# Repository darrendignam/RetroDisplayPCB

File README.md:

# RetroDisplayPCB

This repo is part a wider Tickertape Retro Display project that you can use to create your own Internet of Things LED display with that retro feel.

Check out the website, and my other project for the code library for Arduino and ESP32 for the rest of the project.

* http://tickertape.cc/
* https://github.com/darrendignam/LED_Display_Wrapper

# How the project works

Eagle version 9.1.3 was used on a Windows PC to create these files.
Some of the parts used, were made specifically for this project, and can be found here too.

In addition to the standard libraries the following Eagle libraries were also used:

    holtek-led-controller-v1
    
    Holtek Semiconductor Inc. Devices
    RAM Mapping 16*8 LED Controller Driver with keyscan
    SOP28, SOP24, SOP20
    www.holtek.com
    Created by S.Hofmann mc_sho@gmx.de
    
* http://eagle.autodesk.com/eagle/download/444

Various SparkFun libraries:
    
    SparkFun-Aesthetics
    SparkFun-Capacitors
    SparkFun-Connectors
    SparkFun-LED
    
* https://github.com/sparkfun/SparkFun-Eagle-Libraries
    
All of these are easy to find either in the library manager, or from the github pages for these projects. The sparkfun link has further great information for using Eagle and custom libraries installing them, everything. So I won't try and replicate that here!

# License Information
This library is released under the [Creative Commons ShareAlike 4.0 International license](https://creativecommons.org/licenses/by-sa/4.0/). You are welcome to use this library for commercial purposes. For attribution, we ask that when you begin to sell your device, you email us with a link to the product being sold. It would be great to see where this project goes, and will perhaps feature it on the website.

Together we can help the open-source hardware community continue to thrive and grow!

This project uses the 1206 LED footprint and some other helpful parts from the SparkFun projects listed above to help with the project. None of them were modified, they were used as-is.

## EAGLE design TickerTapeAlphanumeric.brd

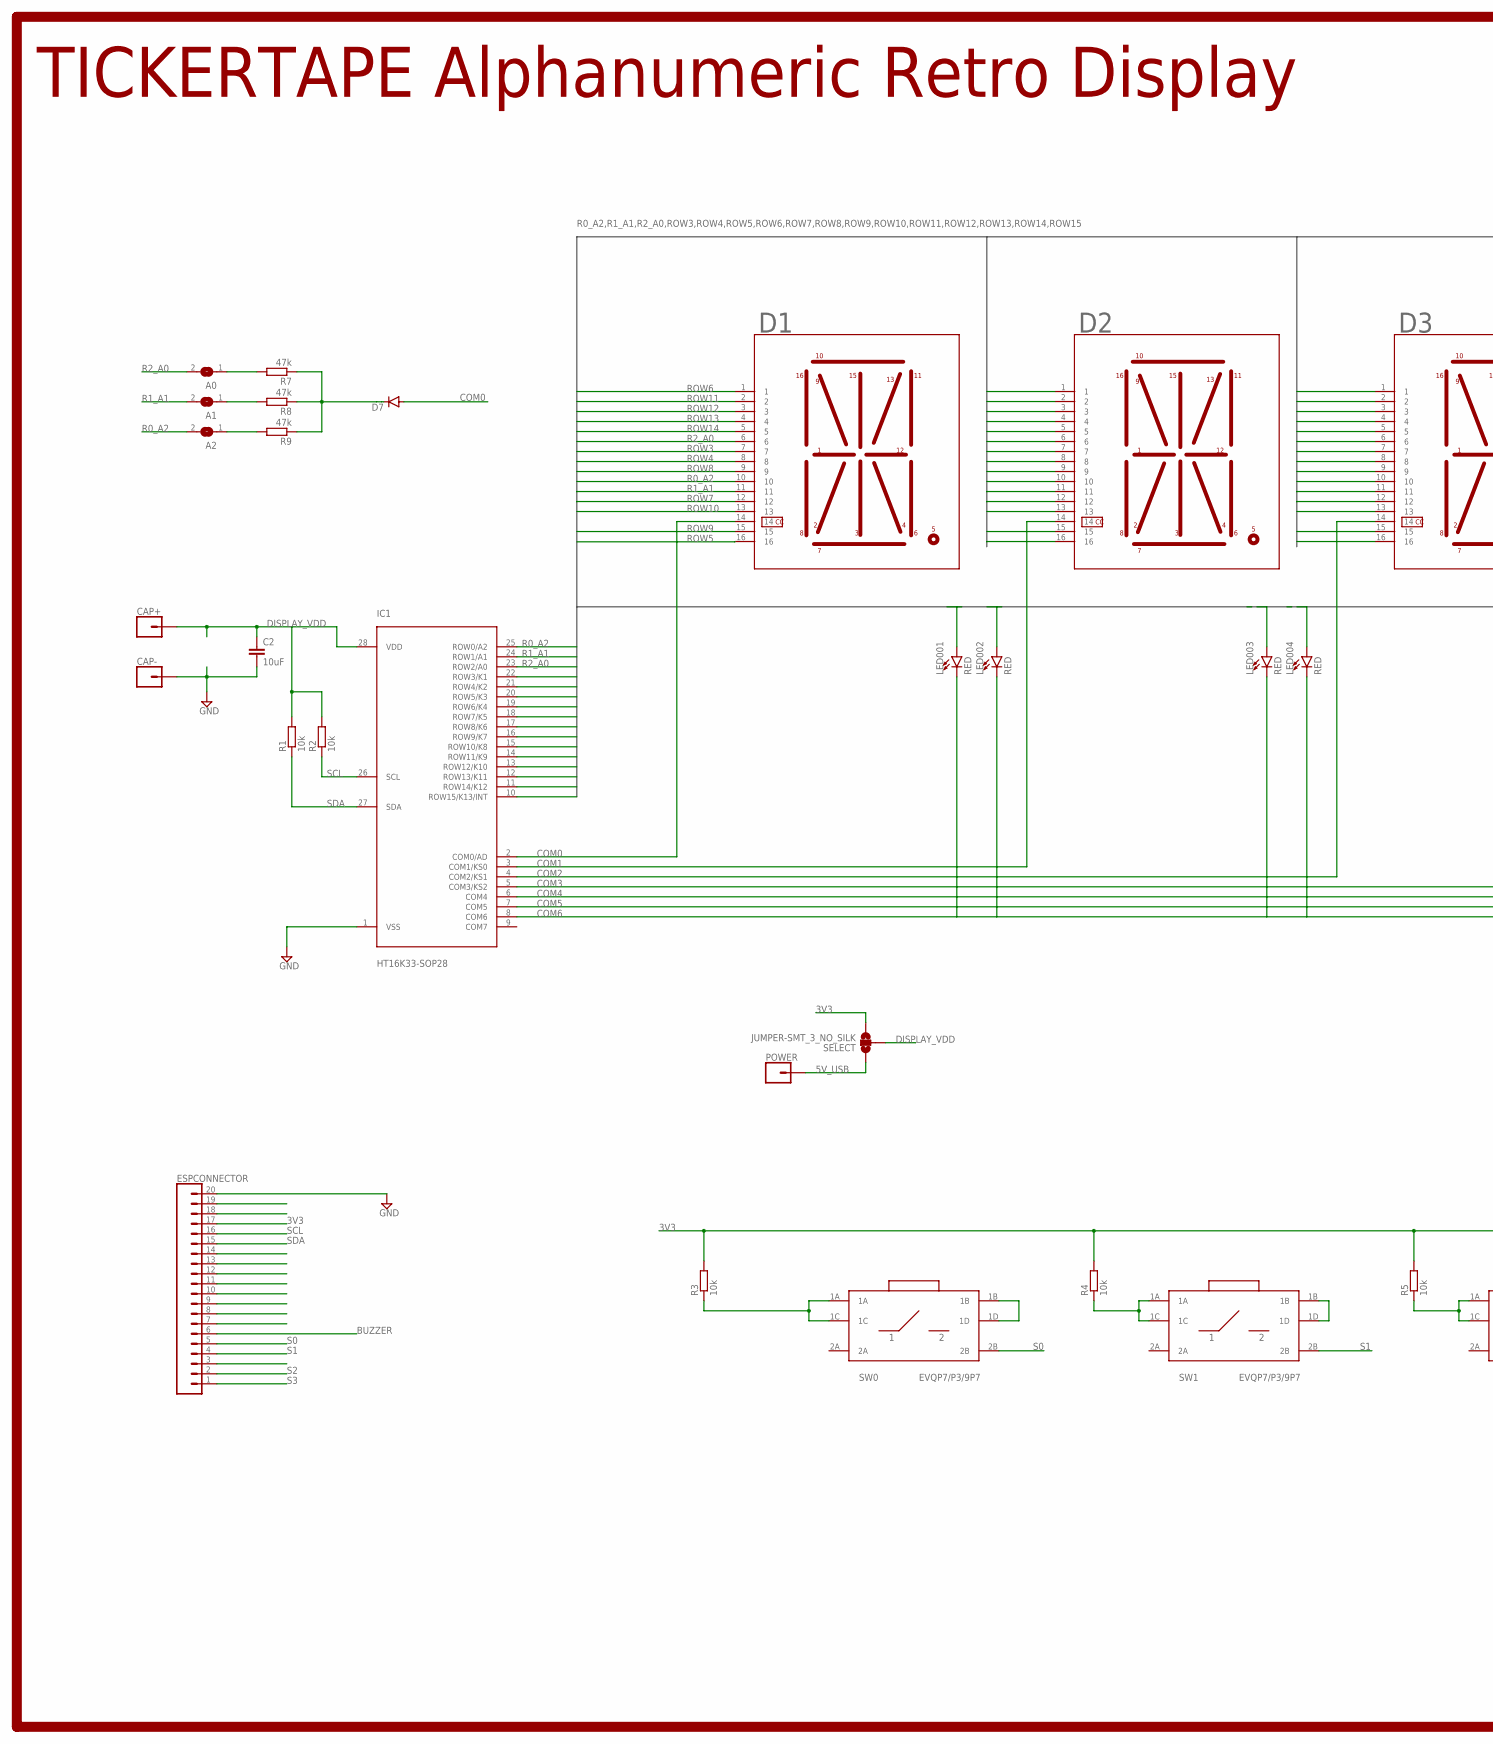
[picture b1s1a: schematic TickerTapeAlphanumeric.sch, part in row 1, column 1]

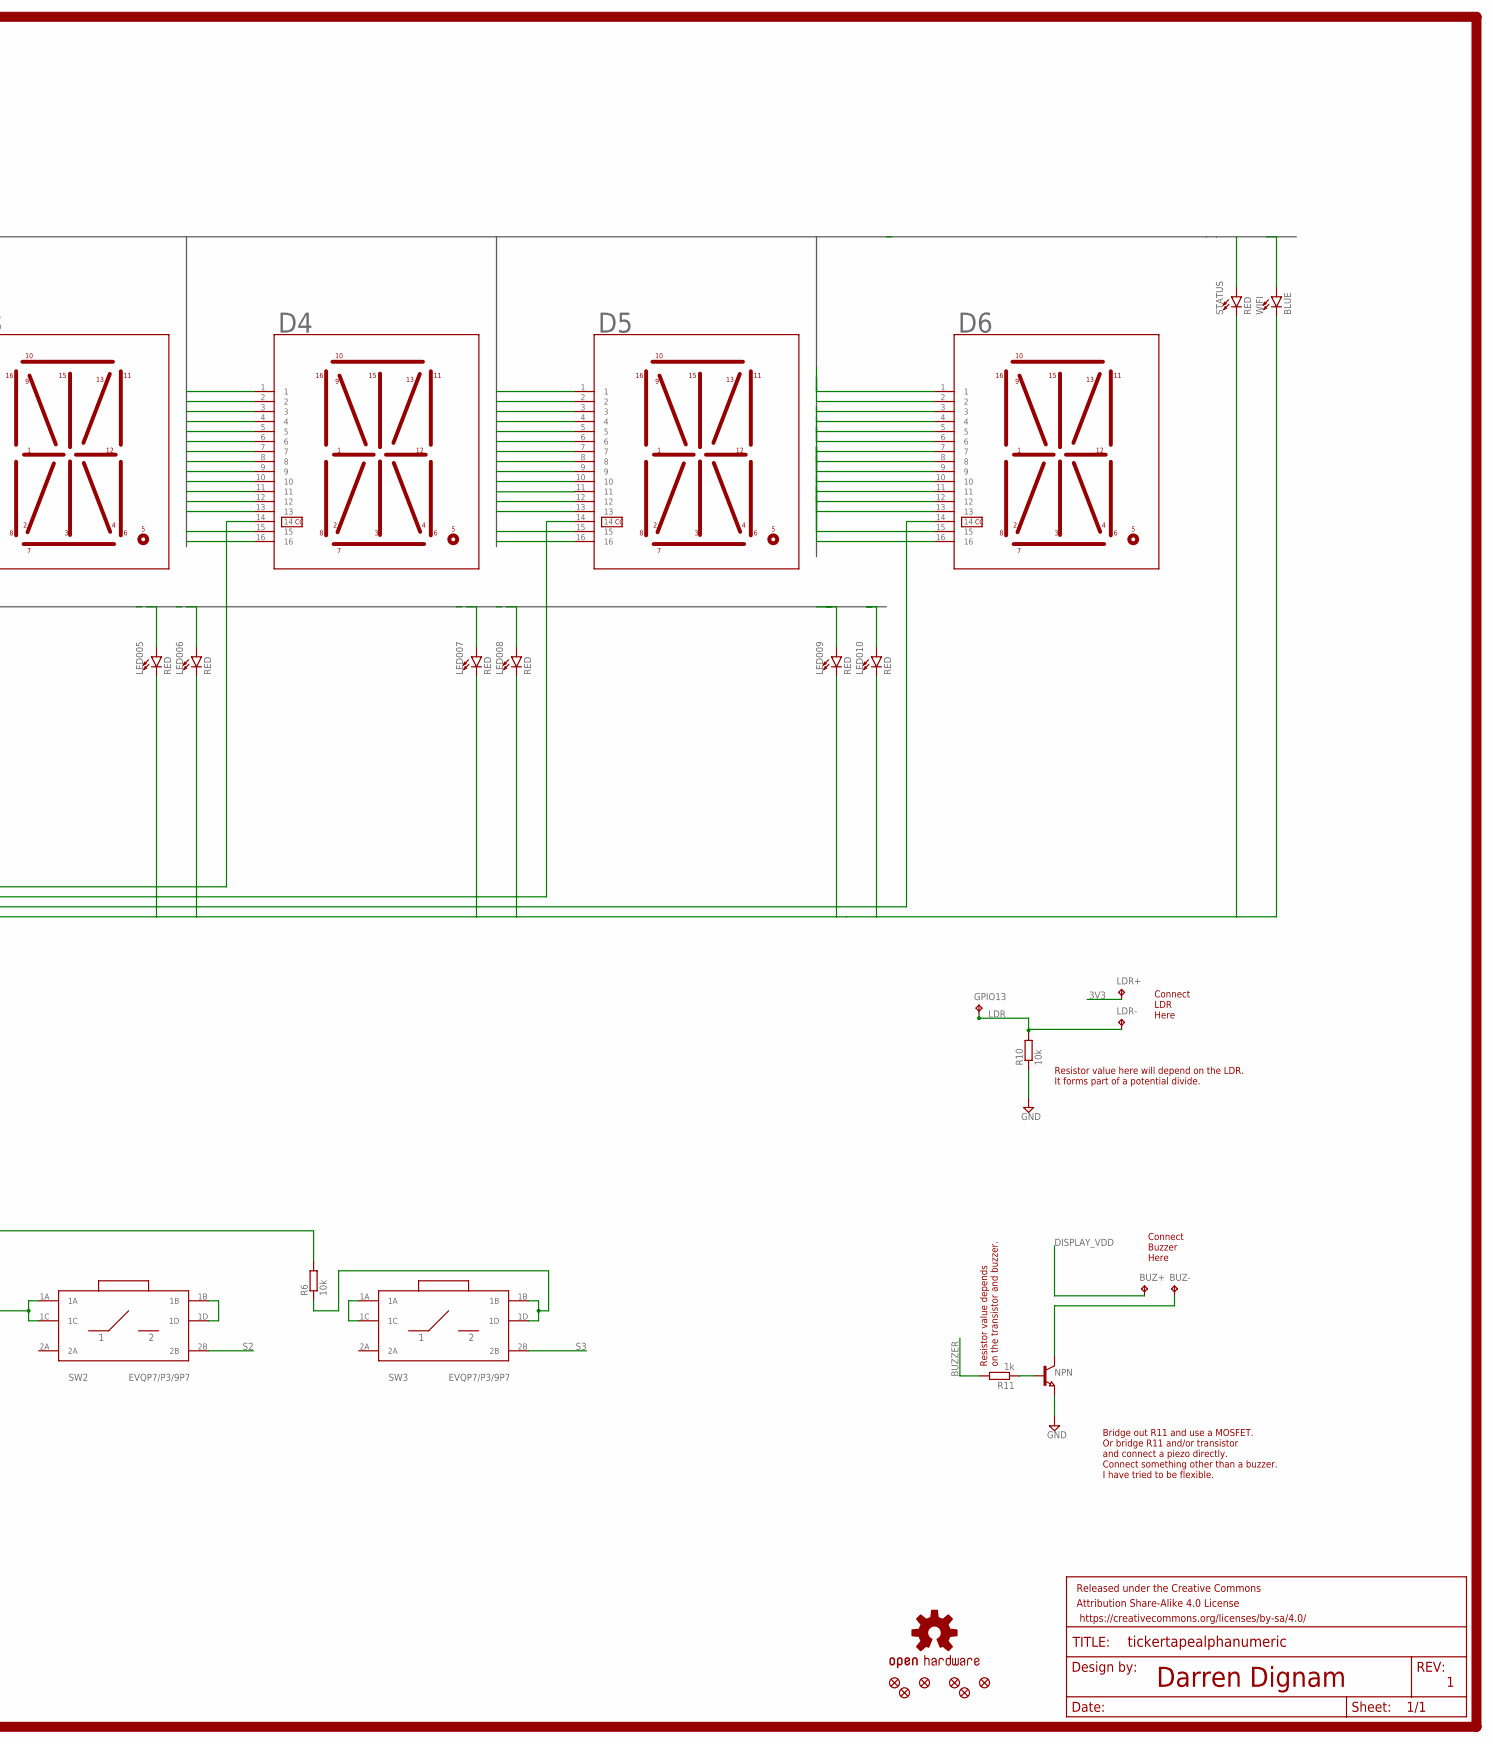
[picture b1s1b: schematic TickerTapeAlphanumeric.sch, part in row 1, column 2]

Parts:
A0, A1, A2: SOLDERJUMPERREFLOW_NOPASTE; SOLDERJUMPER_REFLOW_NOPASTE
BUZ+: TPB1,27; B1,27
BUZ-: TPB1,27; B1,27
C2: 10uF; 1206
CAP+: CONN_01; 1X01
CAP-: CONN_01; 1X01
D1, D2, D3, D4, D5, D6: KCPSC04-105; 14-SEGMENT-LED
D7: DIODE-SOD323-W; SOD323-W
ESPCONNECTOR: CONN_20; 1X20
FD1, FD2, FD3, FD4, FD5, FD6: FIDUCIALUFIDUCIAL; FIDUCIAL-MICRO
FRAME1: FRAME-LEDGER; CREATIVE_COMMONS
GPIO13: TPB1,27; B1,27
IC1: HT16K33-SOP28; SOIC127P1031X264-28N
LDR+: TPB1,27; B1,27
LDR-: TPB1,27; B1,27
LED001, LED002, LED003, LED004, LED005, LED006, LED007, LED008, LED009, LED010: RED; LED-1206
LOGO1: OSHW-LOGOM-COPPER; OSHW-LOGO-M_COPPER
NPN: NPN-TRANSISTOR_SOT23; SOT23
POWER: CONN_01; 1X01
R1, R2, R10: 10k; R1206
R3, R4, R5, R6: 10k; R0603
R7, R8, R9: 47k; R1206
R11: 1k; R1206
SELECT: JUMPER-SMT_3_NO_SILK; SMT-JUMPER_3_NO_SILK
STATUS: RED; LED-1206
SW0, SW1, SW2, SW3: EVQP7/P3/9P7; SMT5.5MMX2.5MM
WIFI: BLUE; LED-1206

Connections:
3V3: ESPCONNECTOR.17, LDR+.TP, R3.2, R4.2, R5.2, R6.2, SELECT.3
5V_USB: POWER.1, SELECT.1
BUZZER: ESPCONNECTOR.6, R11.2
COM0: D1.14, D7.A, IC1.2 (COM0/AD)
COM1: D2.14, IC1.3 (COM1/KS0)
COM2: D3.14, IC1.4 (COM2/KS1)
COM3: D4.14, IC1.5 (COM3/KS2)
COM4: D5.14, IC1.6 (COM4)
COM5: D6.14, IC1.7 (COM5)
COM6: IC1.8 (COM6), LED001.C, LED002.C, LED003.C, LED004.C, LED005.C, LED006.C, LED007.C, LED008.C, LED009.C, LED010.C, STATUS.C, WIFI.C
DISPLAY_VDD: BUZ+.TP, C2.1, CAP+.1, IC1.28 (VDD), R1.2, R2.2, SELECT.2
GND: C2.2, CAP-.1, ESPCONNECTOR.20, IC1.1 (VSS), NPN.2 (E), R10.1
LDR: GPIO13.TP, LDR-.TP, R10.2
unnamed: R3.1, SW0.1A, SW0.1C
unnamed: SW0.1B, SW0.1D
unnamed: R4.1, SW1.1A, SW1.1C
unnamed: SW1.1B, SW1.1D
unnamed: BUZ-.TP, NPN.3 (C)
unnamed: R6.1, SW3.1B, SW3.1D
unnamed: D7.C, R7.1, R8.1, R9.1
unnamed: A0.1, R7.2
unnamed: A1.1, R8.2
unnamed: R5.1, SW2.1A, SW2.1C
unnamed: SW2.1B, SW2.1D
unnamed: SW3.1A, SW3.1C
unnamed: A2.1, R9.2
unnamed: NPN.1 (B), R11.1
R0_A2: A2.2, D1.10, D2.10, D3.10, D4.10, D5.10, D6.10, IC1.25 (ROW0/A2), LED001.A
R1_A1: A1.2, D1.11, D2.11, D3.11, D4.11, D5.11, D6.11, IC1.24 (ROW1/A1), LED002.A
R2_A0: A0.2, D1.6, D2.6, D3.6, D4.6, D5.6, D6.6, IC1.23 (ROW2/A0), LED003.A
ROW3: D1.7, D2.7, D3.7, D4.7, D5.7, D6.7, IC1.22 (ROW3/K1), LED004.A
ROW4: D1.8, D2.8, D3.8, D4.8, D5.8, D6.8, IC1.21 (ROW4/K2), LED005.A
ROW5: D1.16, D2.16, D3.16, D4.16, D5.16, D6.16, IC1.20 (ROW5/K3), LED006.A
ROW6: D1.1, D2.1, D3.1, D4.1, D5.1, D6.1, IC1.19 (ROW6/K4), LED007.A
ROW7: D1.12, D2.12, D3.12, D4.12, D5.12, D6.12, IC1.18 (ROW7/K5), LED008.A
ROW8: D1.9, D2.9, D3.9, D4.9, D5.9, D6.9, IC1.17 (ROW8/K6), LED009.A
ROW9: D1.15, D2.15, D3.15, D4.15, D5.15, D6.15, IC1.16 (ROW9/K7), LED010.A
ROW10: D1.13, D2.13, D3.13, D4.13, D5.13, D6.13, IC1.15 (ROW10/K8), STATUS.A
ROW11: D1.2, D2.2, D3.2, D4.2, D5.2, D6.2, IC1.14 (ROW11/K9), WIFI.A
ROW12: D1.3, D2.3, D3.3, D4.3, D5.3, D6.3, IC1.13 (ROW12/K10)
ROW13: D1.4, D2.4, D3.4, D4.4, D5.4, D6.4, IC1.12 (ROW13/K11)
ROW14: D1.5, D2.5, D3.5, D4.5, D5.5, D6.5, IC1.11 (ROW14/K12)
ROW15: IC1.10 (ROW15/K13/INT)
S0: ESPCONNECTOR.5, SW0.2B
S1: ESPCONNECTOR.4, SW1.2B
S2: ESPCONNECTOR.2, SW2.2B
S3: ESPCONNECTOR.1, SW3.2B
SCL: ESPCONNECTOR.16, IC1.26 (SCL), R2.1
SDA: ESPCONNECTOR.15, IC1.27 (SDA), R1.1

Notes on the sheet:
TICKERTAPE Alphanumeric Retro Display
Darren Dignam
Connect LDR Here
Connect Buzzer Here
Resistor value here will depend on the LDR. It forms part of a potential divide.
Resistor value depends on the transistor and buzzer.
Bridge out R11 and use a MOSFET. Or bridge R11 and/or transistor and connect a piezo directly. Connect something other than a buzzer. I have tried to be flexible.

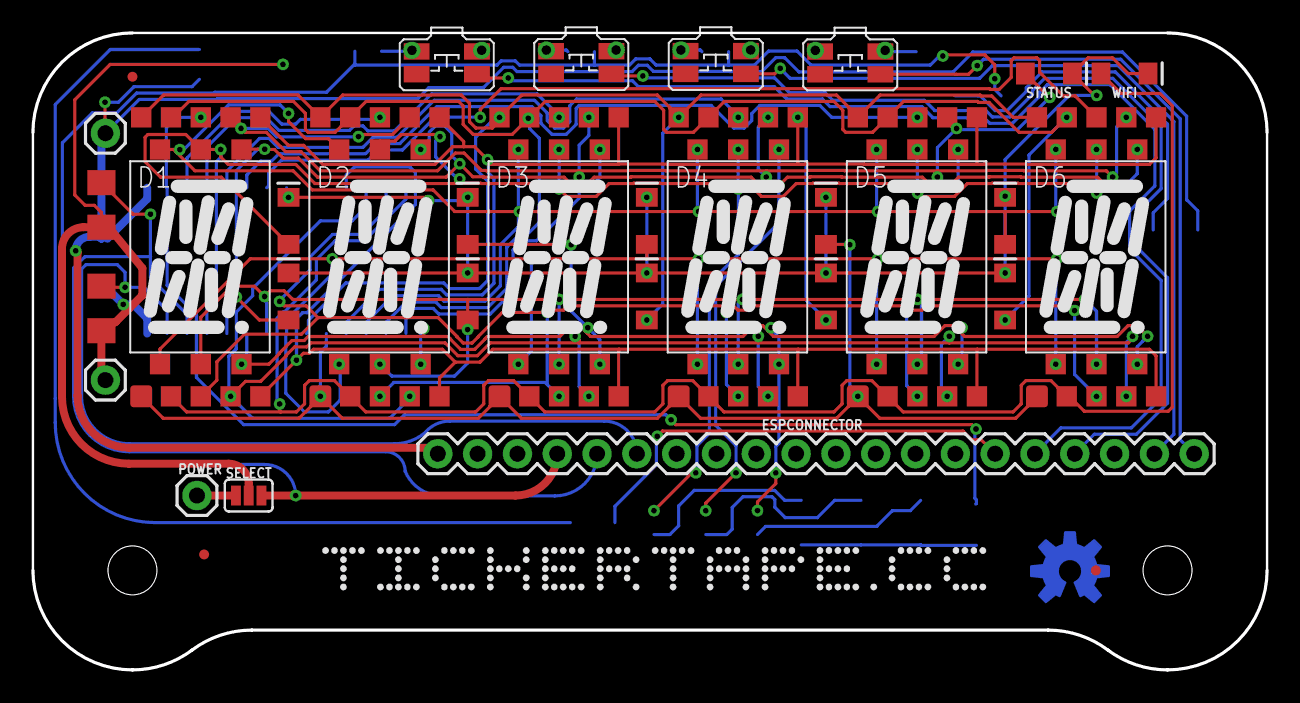
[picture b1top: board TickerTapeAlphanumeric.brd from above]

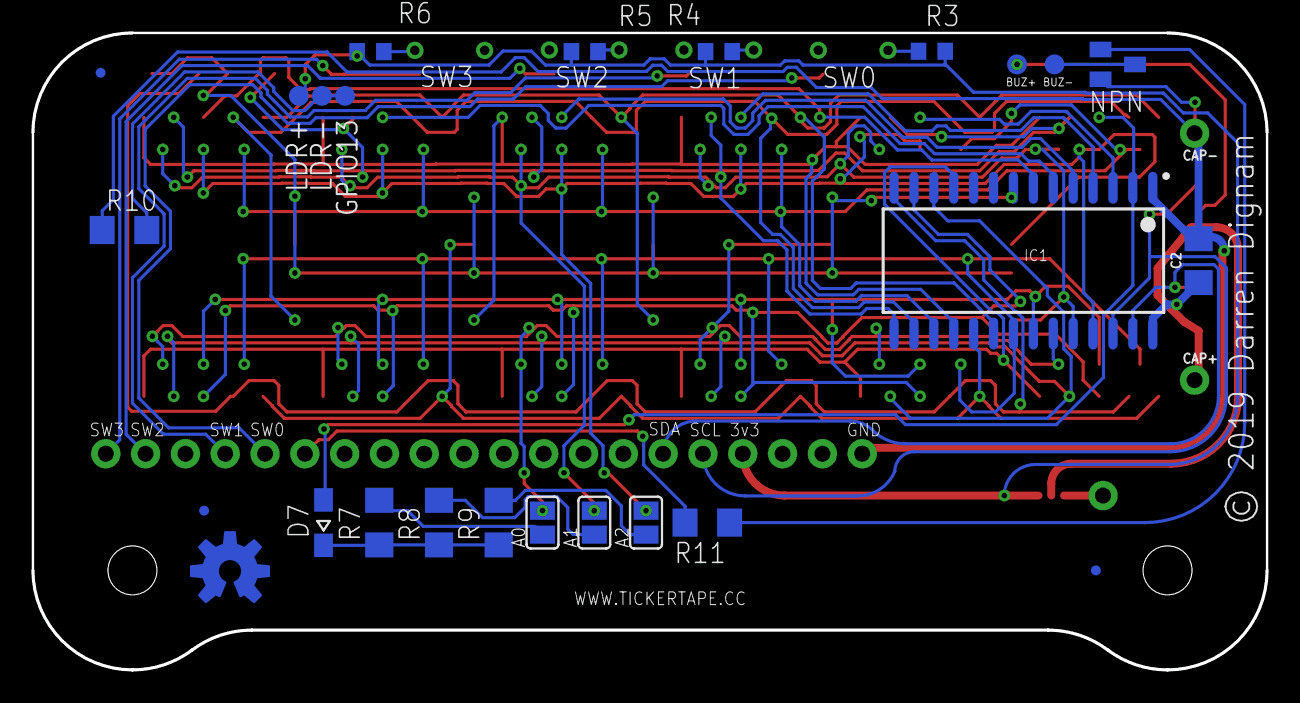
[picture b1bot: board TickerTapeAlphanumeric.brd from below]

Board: 2 copper layers, 78.7 x 40.6 mm, 58 parts (25 on the bottom side), 48 nets.

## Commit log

2019-03-13 Tickertape Retro Display initial commit.
2019-03-13 Update README.md
    Added more info the the readme file
2019-03-13 Update README.md
    Added some license info

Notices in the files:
TickerTapeAlphanumeric.brd:
© 2019 Darren Dignam
parts and their libraries:
SparkFun-Capacitors: Licensing: Creative Commons ShareAlike 4.0 International - https://creativecommons.org/licenses/by-sa/4.0
SparkFun-Aesthetics: Released under the Creative Commons Attribution Share-Alike 4.0 License
